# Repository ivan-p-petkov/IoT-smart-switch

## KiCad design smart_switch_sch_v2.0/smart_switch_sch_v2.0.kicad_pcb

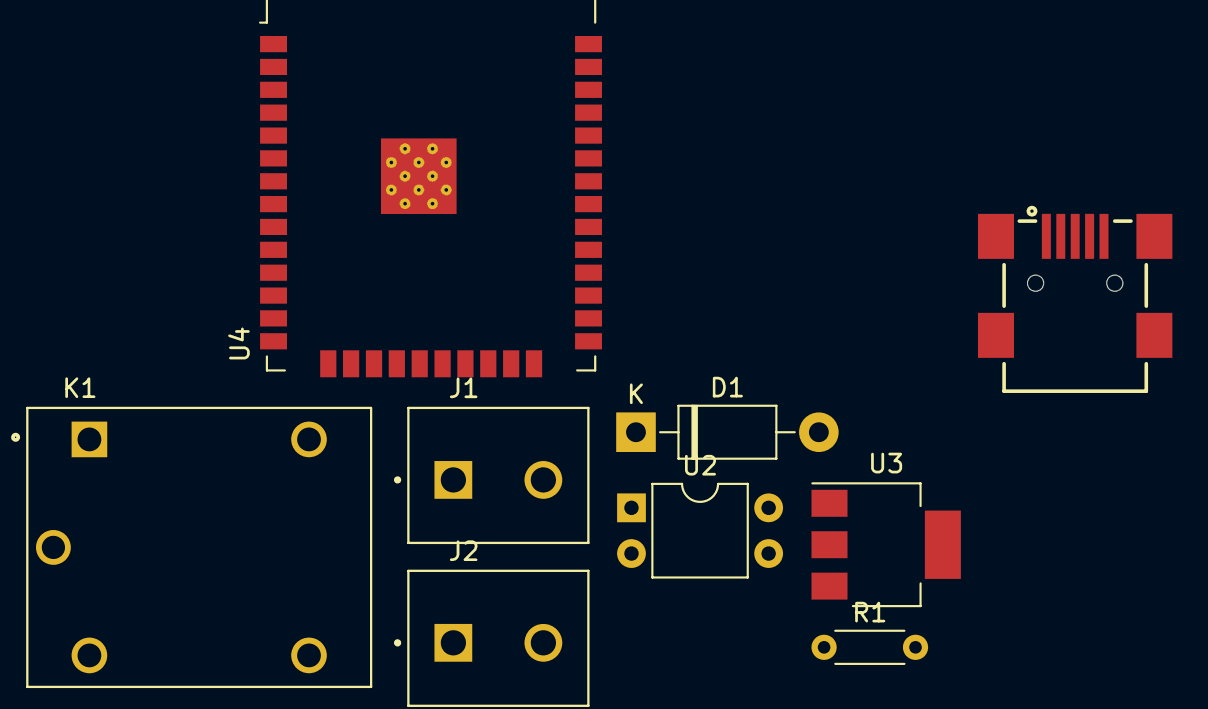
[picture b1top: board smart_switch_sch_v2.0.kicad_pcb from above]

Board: 2 copper layers, 9 parts (0 on the bottom side), 7 nets, no tracks yet.

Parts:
D1: 1N4007; D_DO-41_SOD81_P10.16mm_Horizontal
J1, J2: KF301-2P; HANDSON_KF301-2P
J3: 65100516121; usb_mini
K1: SRD-05VDC-SL-C; RELAY_SRD-05VDC-SL-C
R1: 180Ω; R_Axial_DIN0204_L3.6mm_D1.6mm_P5.08mm_Horizontal
U2: PC817; DIP-4_W7.62mm
U3: AMS1117-3.3; SOT-223-3_TabPin2
U4: ESP32-WROOM-32

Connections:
+3.3V: U3.2 (VO), U4.2 (VDD), U4.3 (EN)
+5V: J1.2, J3.1 (VBUS), U2.4, U3.3 (VI)
GND: D1.2 (A), J1.1, J3.5 (GND), J3.S1, J3.S2, J3.S3, J3.S4, K1.A2, U2.2, U3.1 (GND), U4.1 (GND), U4.15 (GND), U4.38 (GND), U4.39 (GND)
unnamed: D1.1 (K), K1.A1, U2.3
unnamed: J2.1, K1.NO
unnamed: J2.2, K1.COM
unnamed: R1.2, U2.1

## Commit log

2024-03-21 Add README file
2024-03-21 Esp32 code for the remote switch
2024-03-22 smart switch scheme and pcb
2024-03-28 smart switch scheme version 1.0
2024-03-28 smart switch scheme and pcb version 1.0
2024-03-28 smart switch scheme and pcb version 2.0
